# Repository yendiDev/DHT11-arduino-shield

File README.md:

# Temperature and Humidity Sensor Arduino Shield

This Arduino UNO shield integrates a DHT11 temperature and humidity sensor together with a 16x2 LCD display for visualisation. It also includes a potentiometer for controlling the brightness of the LCD, and an LED which can be used in anyway one could imagine 

Below are screenshots of the PCB:

### Schematics:

### PCB Layout:
Front layer:

Bottom layer:

### 3D view of PCB:

## Programming the Shield

```C++
#include <DHT.h>
#include <LiquidCrystal.h>

// pin definitions
#define DHT_PIN 2          // dht11 sensor pin
#define LED_PIN 13         // led indicator pin
#define DHTTYPE DHT11      // dht11 sensor type

// lcd pins
const int rs = 11, en = 12;
const int d4 = 5, d5 = 4, d6 = 3, d7 = 2;

// initialize components
DHT dht(DHT_PIN, DHTTYPE);
LiquidCrystal lcd(rs, en, d4, d5, d6, d7);

void setup() {
  // initialize serial communication
  Serial.begin(9600);
  
  // initialize the dht sensor
  dht.begin();
  
  // set up the lcd
  lcd.begin(16, 2);  // 16x2 lcd
  
  // initialize led pin
  pinMode(LED_PIN, OUTPUT);
  
  // initial lcd message
  lcd.print("Temp & Humidity");
  lcd.setCursor(0, 1);
  lcd.print("Initializing...");
  
  // wait for sensor to stabilize
  delay(2000);
}

void loop() {
  // read temperature and humidity
  float humidity = dht.readHumidity();
  float temperature = dht.readTemperature();
  
  // check if reads failed and exit early (will try again)
  if (isnan(humidity) || isnan(temperature)) {
    lcd.clear();
    lcd.print("Sensor Error!");
    digitalWrite(LED_PIN, HIGH);  // led on indicates error
    delay(2000);
    return;
  }
  
  // clear led if reading successful
  digitalWrite(LED_PIN, LOW);
  
  // update lcd
  lcd.clear();
  lcd.setCursor(0, 0);
  lcd.print("Temp: ");
  lcd.print(temperature, 1);
  lcd.print((char)223);  // degree symbol
  lcd.print("C");
  
  lcd.setCursor(0, 1);
  lcd.print("Humidity: ");
  lcd.print(humidity, 1);
  lcd.print("%");
  
  // also send to serial monitor
  Serial.print("Temperature: ");
  Serial.print(temperature);
  Serial.print(" °C, Humidity: ");
  Serial.print(humidity);
  Serial.println("%");
  
  // wait before next reading
  delay(2000);
}
```

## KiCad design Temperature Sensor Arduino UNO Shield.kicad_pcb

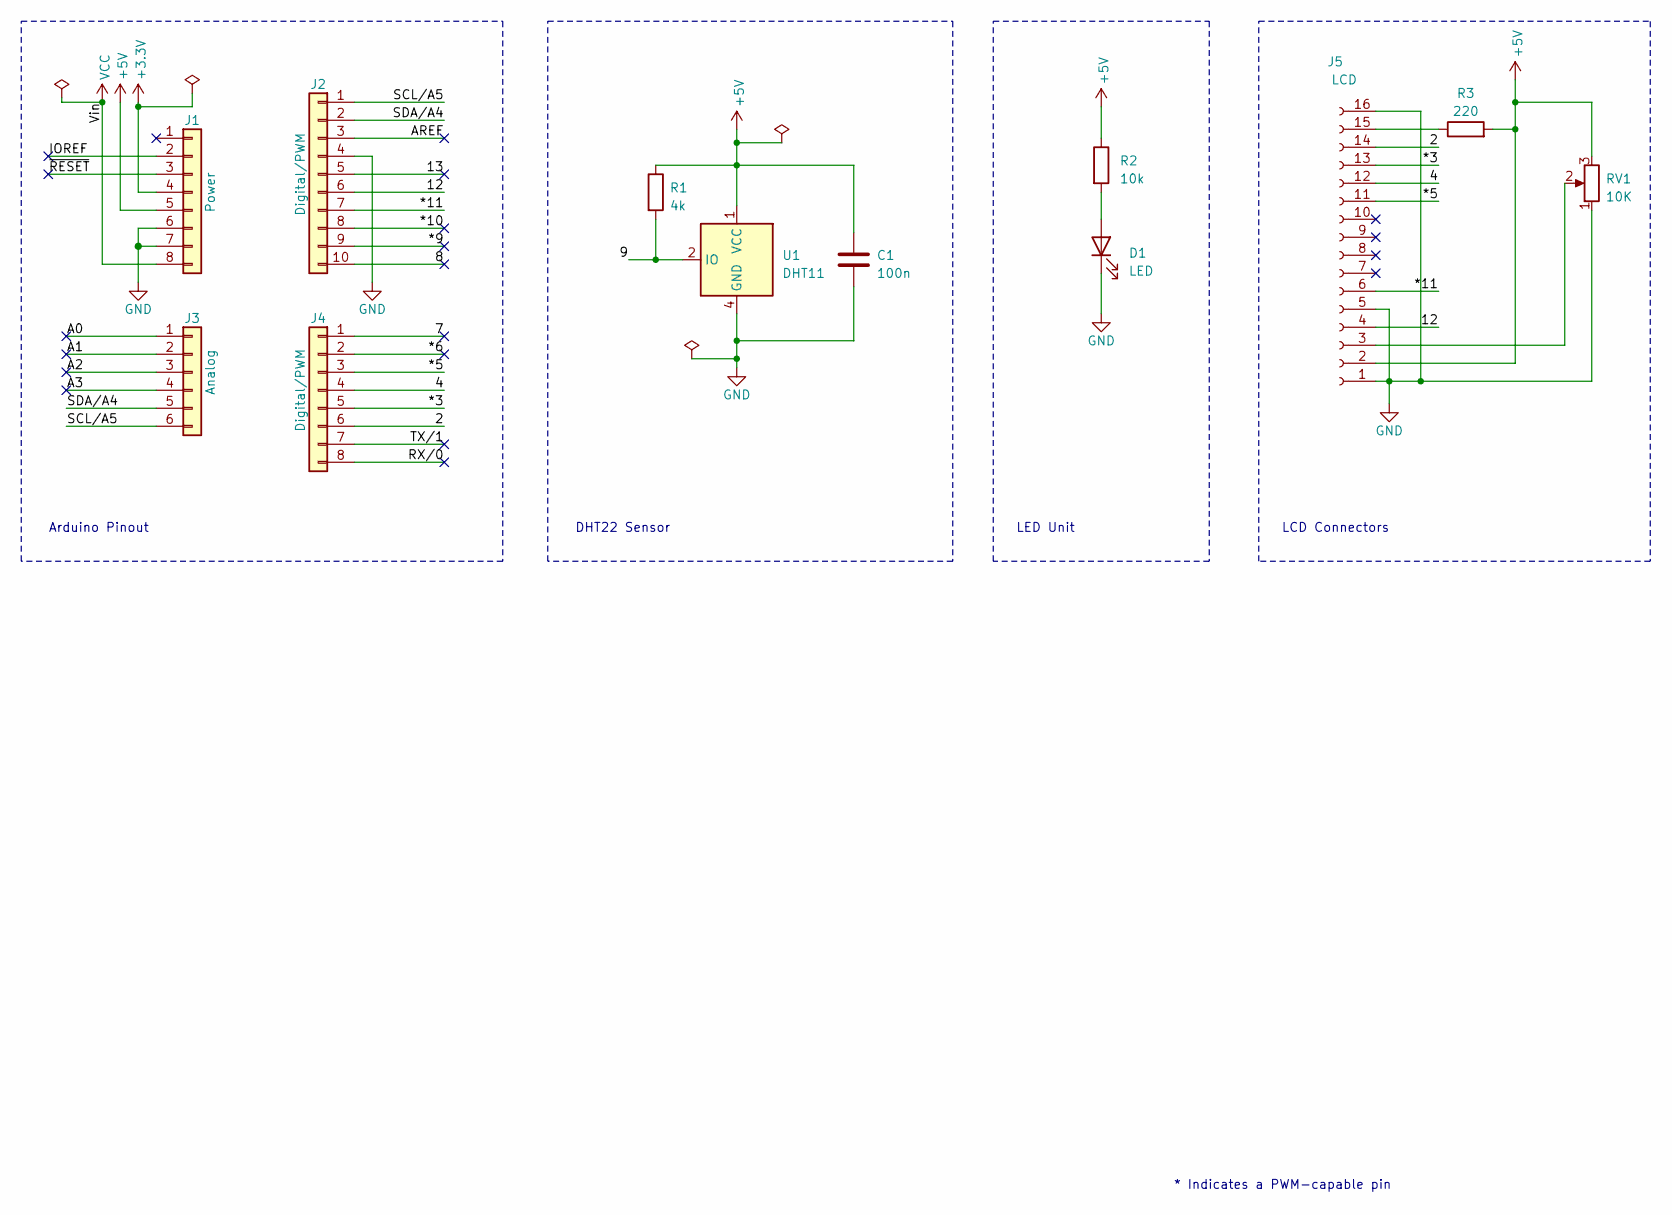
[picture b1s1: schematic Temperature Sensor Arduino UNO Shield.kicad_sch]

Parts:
C1: 100n; CP_Axial_L10.0mm_D4.5mm_P15.00mm_Horizontal
D1: LED; LED_D3.0mm
J1: Power; PinSocket_1x08_P2.54mm_Vertical
J2: Digital/PWM; PinSocket_1x10_P2.54mm_Vertical
J3: Analog; PinSocket_1x06_P2.54mm_Vertical
J4: Digital/PWM; PinSocket_1x08_P2.54mm_Vertical
J5: LCD; PinSocket_1x16_P2.54mm_Vertical
R1: 4k; R_Axial_DIN0204_L3.6mm_D1.6mm_P5.08mm_Horizontal
R2: 10k; R_Axial_DIN0204_L3.6mm_D1.6mm_P5.08mm_Horizontal
R3: 220; R_Axial_DIN0204_L3.6mm_D1.6mm_P5.08mm_Horizontal
RV1: 10K; Potentiometer_Bourns_3266W_Vertical
U1: DHT11; Aosong_DHT11_5.5x12.0_P2.54mm

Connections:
+3V3: J1.4
+5V: C1.1, J1.5, J5.2, R1.1, R2.1, R3.2, RV1.3, U1.1 (VCC)
/2: J4.6, J5.14
/4: J4.4, J5.12
/7: J4.1
/8: J2.10
/9: R1.2, U1.2 (IO)
/12: J2.6, J5.4
/13: J2.5
/*3: J4.5, J5.13
/*5: J4.3, J5.11
/*6: J4.2
/*9: J2.9
/*10: J2.8
/*11: J2.7, J5.6
/A0: J3.1
/A1: J3.2
/A2: J3.3
/A3: J3.4
/AREF: J2.3
/IOREF: J1.2
/RX/0: J4.8
/SCL/A5: J2.1, J3.6
/SDA/A4: J2.2, J3.5
/TX/1: J4.7
/~RESET: J1.3
GND: C1.2, D1.1 (K), J1.6, J1.7, J2.4, J5.1, J5.5, J5.16, RV1.1, U1.4 (GND)
unnamed: D1.2 (A), R2.2
unnamed: J5.3, RV1.2
unnamed: J5.15, R3.1
VCC: J1.8

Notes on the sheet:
LCD Connectors
LED Unit
DHT22 Sensor
Arduino Pinout
* Indicates a PWM-capable pin

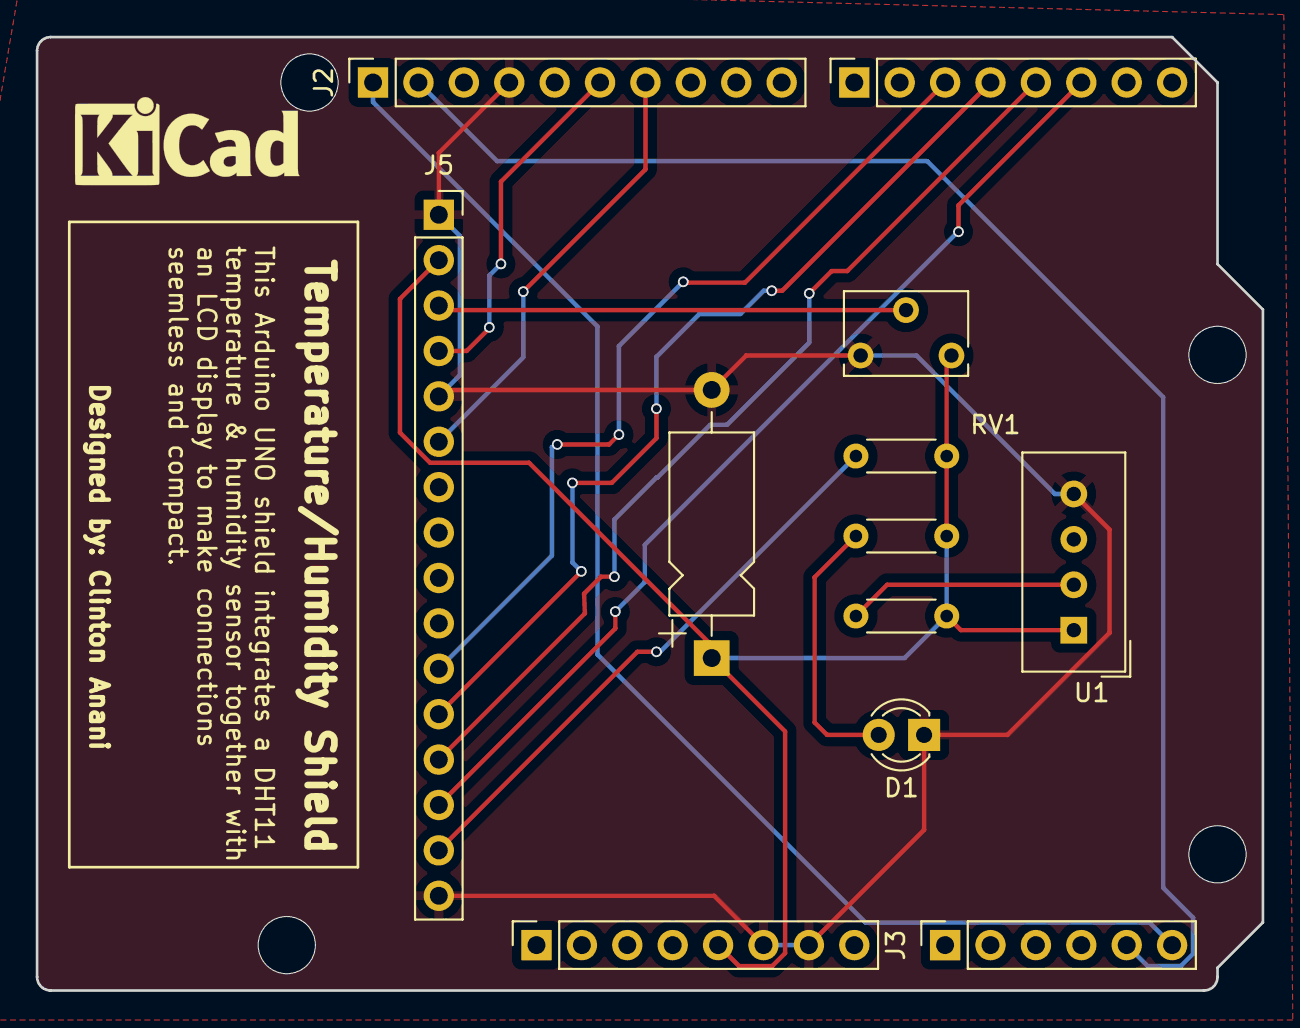
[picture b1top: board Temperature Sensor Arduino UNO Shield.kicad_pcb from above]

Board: 2 copper layers, 68.6 x 53.3 mm, 16 parts (0 on the bottom side), 14 nets.

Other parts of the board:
MH1, MH2, MH3, MH4: MountingHole_3.2mm
